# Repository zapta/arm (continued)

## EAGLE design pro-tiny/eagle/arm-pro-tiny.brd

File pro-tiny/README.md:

ARM PRO TINY
============

### OVERVIEW

TBD.

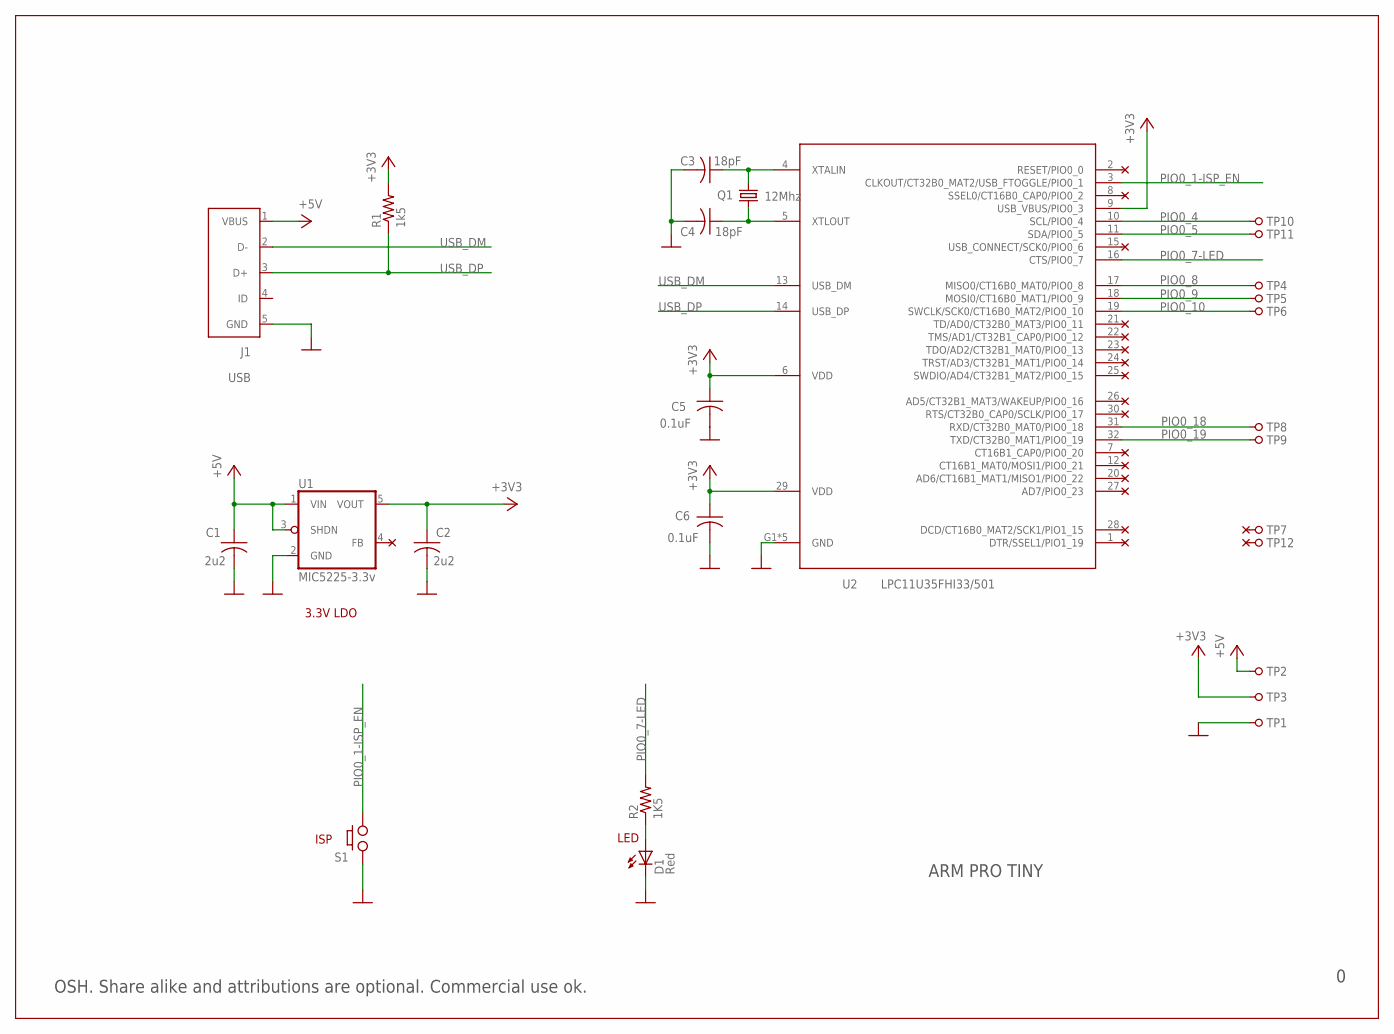
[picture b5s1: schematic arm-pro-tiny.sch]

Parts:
C1, C2: 2u2; C0402K
C3, C4: 18pF; C0402K
C5, C6: 0.1uF; C0402K
D1: Red; CHIP-LED0603
J1: USB; USB-MICRO-ZX62RD-AB-5P8
Q1: 12Mhz; CRYSTAL
R1: 1k5; R0402
R2: 1K5; R0402
S1: PUSH_BUTTON
TP1, TP2, TP3, TP4, TP5, TP6, TP7, TP8, TP9, TP10, TP11, TP12: HDR1; 1X01
U1: MIC5225-3.3v; SOT25
U2: LPC11U35FHI33/501; HVQFN33-5MM

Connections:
+3V3: C2.1, C5.1, C6.1, R1.2, TP3.1, U1.5 (VOUT), U2.6 (VDD), U2.9 (USB_VBUS/PIO0_3), U2.29 (VDD)
+5V: C1.1, J1.1 (VBUS), TP2.1, U1.1 (VIN), U1.3 (SHDN)
GND: C1.2, C2.2, C3.2, C4.2, C5.2, C6.2, D1.C, J1.5 (GND), S1.A1 (1), TP1.1, U1.2 (GND), U2.G1 (GND), U2.G2 (GND), U2.G3 (GND), U2.G4 (GND), U2.TAB (GND)
unnamed: C3.1, Q1.3 (2), U2.4 (XTALIN)
unnamed: C4.1, Q1.1, U2.5 (XTLOUT)
unnamed: D1.A, R2.1
PIO0_1-ISP_EN: S1.B2 (2), U2.3 (CLKOUT/CT32B0_MAT2/USB_FTOGGLE/PIO0_1)
PIO0_4: TP10.1, U2.10 (SCL/PIO0_4)
PIO0_5: TP11.1, U2.11 (SDA/PIO0_5)
PIO0_7-LED: R2.2, U2.16 (CTS/PIO0_7)
PIO0_8: TP4.1, U2.17 (MISO0/CT16B0_MAT0/PIO0_8)
PIO0_9: TP5.1, U2.18 (MOSI0/CT16B0_MAT1/PIO0_9)
PIO0_10: TP6.1, U2.19 (SWCLK/SCK0/CT16B0_MAT2/PIO0_10)
PIO0_18: TP8.1, U2.31 (RXD/CT32B0_MAT0/PIO0_18)
PIO0_19: TP9.1, U2.32 (TXD/CT32B0_MAT1/PIO0_19)
USB_DM: J1.2 (D-), U2.13 (USB_DM)
USB_DP: J1.3 (D+), R1.1, U2.14 (USB_DP)

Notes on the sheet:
ARM PRO TINY
ISP
LED
3.3V LDO
OSH. Share alike and attributions are optional. Commercial use ok.

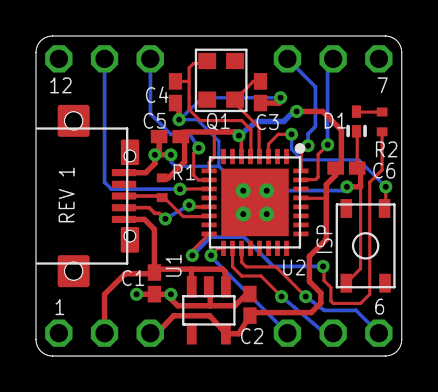
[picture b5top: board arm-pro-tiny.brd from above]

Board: 2 copper layers, 20.3 x 17.8 mm, 26 parts (0 on the bottom side), 17 nets.

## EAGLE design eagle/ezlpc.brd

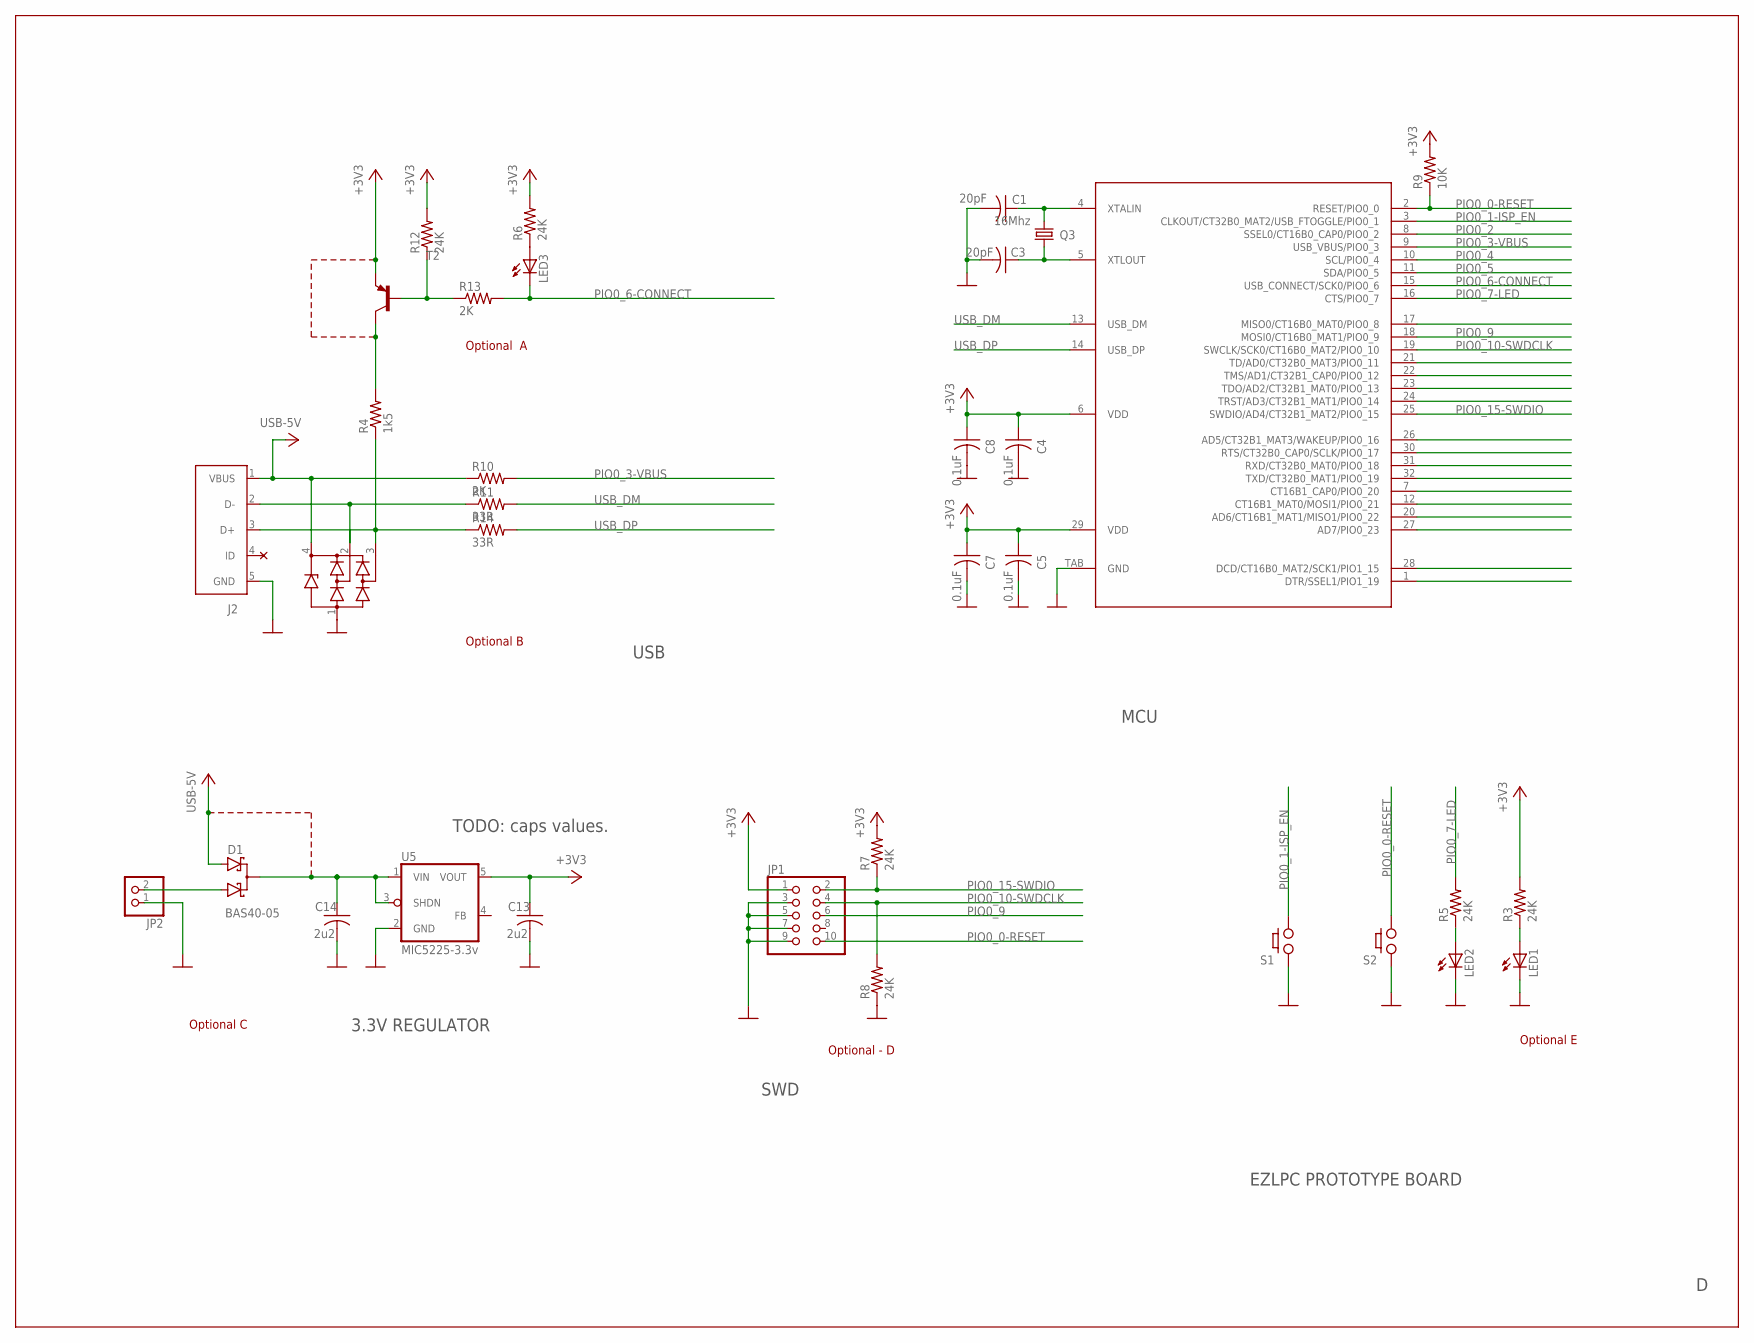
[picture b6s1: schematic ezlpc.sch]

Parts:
C1, C3: 20pF; C0603
C4, C5, C7, C8: 0.1uF; C0603
C13, C14: 2u2; C0603
D1: BAS40-05; SOT23
J2: USB; USB-MICRO-ZX62RD-AB-5P8
JP1: SWD-HEADER
JP2: PINHD-1X2; 1X02
LED1, LED2, LED3: LEDCHIP-LED0603; CHIP-LED0603
Q3: 16Mhz; CRYSTAL-CTS406
R3, R5, R6, R7, R8, R12: 24K; R0402
R4: 1k5; R0402
R9: 10K; R0402
R10, R13: 2K; R0402
R11, R14: 33R; R0402
S1, S2: PUSH_BUTTON
T2: BC857B-PNP-SOT23-BEC; SOT23-BEC
U4: LPC11U35FHN33/501; HVQFN33-5MM
U5: MIC5225-3.3v; SOT25
U$5: PRTR5VOU2X; SOT143B

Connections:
+3V3: C4.1, C5.1, C7.1, C8.1, C13.1, JP1.1, R3.2, R6.2, R7.2, R9.2, R12.2, T2.E, U4.6 (VDD), U4.29 (VDD), U5.5 (VOUT)
GND: C1.2, C3.2, C4.2, C5.2, C7.2, C8.2, C13.2, C14.2, J2.5 (GND), JP1.3, JP1.5, JP1.7, JP1.9, JP2.1, LED1.C, LED2.C, R8.1, S1.A1 (1), S2.A1 (1), U4.TAB (GND), U5.2 (GND), U$5.1 (GND)
unnamed: C1.1, Q3.1, U4.4 (XTALIN)
unnamed: LED1.A, R3.1
unnamed: C3.1, Q3.3 (2), U4.5 (XTLOUT)
unnamed: R12.1, R13.1, T2.B
unnamed: R4.2, T2.C
unnamed: LED2.A, R5.1
unnamed: LED3.A, R6.1
unnamed: J2.2 (D-), J2.3 (D+), R4.1, R11.1, R14.1, U$5.2 (IO1), U$5.3 (IO2)
unnamed: C14.1, D1.3 (C), U5.1 (VIN), U5.3 (SHDN)
unnamed: D1.1 (A1), JP2.2
PIO0_0-RESET: JP1.10, R9.1, S2.B2 (2), U4.2 (RESET/PIO0_0)
PIO0_1-ISP_EN: S1.B2 (2), U4.3 (CLKOUT/CT32B0_MAT2/USB_FTOGGLE/PIO0_1)
PIO0_2: U4.8 (SSEL0/CT16B0_CAP0/PIO0_2)
PIO0_3-VBUS: R10.2, U4.9 (USB_VBUS/PIO0_3)
PIO0_4: U4.10 (SCL/PIO0_4)
PIO0_5: U4.11 (SDA/PIO0_5)
PIO0_6-CONNECT: LED3.C, R13.2, U4.15 (USB_CONNECT/SCK0/PIO0_6)
PIO0_7-LED: R5.2, U4.16 (CTS/PIO0_7)
PIO0_9: JP1.6, U4.18 (MOSI0/CT16B0_MAT1/PIO0_9)
PIO0_10-SWDCLK: JP1.4, R8.2, U4.19 (SWCLK/SCK0/CT16B0_MAT2/PIO0_10)
PIO0_15-SWDIO: JP1.2, R7.1, U4.25 (SWDIO/AD4/CT32B1_MAT2/PIO0_15)
USB-5V: D1.2 (A2), J2.1 (VBUS), R10.1, U$5.4 (VCC)
USB_DM: R11.2, U4.13 (USB_DM)
USB_DP: R14.2, U4.14 (USB_DP)

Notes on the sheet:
TODO: caps values.
EZLPC PROTOTYPE BOARD
MCU
3.3V REGULATOR
USB
SWD
Optional B
Optional C
Optional - D
Optional E
Optional A

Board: 2 copper layers, 34 parts (0 on the bottom side), 23 nets, no tracks yet.

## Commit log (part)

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2014-10-01 First iteration of the ezlpc lib.
2014-10-01 Moved the delay function out of main.
2014-10-02 Added LPC11U3X documentation.
2014-10-06 Very early draft of the PCB.
2014-10-06 More progress with the library. Still an early draft.
2014-10-10 Initial placement.
2014-10-11 Imprived the placement. Now can auto route 100%.
2014-10-11 Extracted self library from the schema.
2014-10-12 Ready for final auto routing.
2014-10-12 More layout cleanup.
2014-10-12 Change via mask limit to 20 mils.
2014-10-12 Added layout pdf.
2014-10-14 Added BOM.
2014-10-14 Updated BOM
2014-10-14 Turned the SWD connector
2014-10-14 Tweaked the silk screen layer.
2014-10-14 Cleaned up ERC warnings.
2014-10-14 Renamed eagle files from ezlpc-proto to arm-mini-pro. Yet to do the same for the firmware.
2014-10-14 Added pdf files.
2014-10-18 Generated gerbers using Elecrow 2 layers CAM files.
2014-10-19 Added a few resources.
2014-11-07 Copied eagle files to new location (pro-mini)
2014-11-07 Updated layout pdf.
2014-11-08 Added 3D print model for a case.
2014-11-08 Added TODO file.
2014-11-08 Added lpcxpresso files.
2014-11-08 Added resource files.
2014-11-09 Assorted cleanups.
2014-11-09 Left overs from previous checkin.
2014-11-10 Fixed location of RST and ISP switches labels (were swapped in the layout). Added labels for GND, 5V and 3V3 pins. No semantic change. Made the gerber files obsolete. Will generate new ones.
2014-11-10 Minor comment change. No semantic change.
2014-12-10 Added two precompiled hello world binaries for the Getting Started procedure.
2014-12-11 Hello world now use \r\n EOL terminator for dump serial port dumpers.
2014-12-17 Added first installment of the README file. Minor BOM update.
2014-12-17 Another table experiment.
2014-12-17 Udpated quick start 1.
2014-12-17 Added link
2014-12-17 Readme update
2014-12-17 Readme updated.
2014-12-17 Readme update.
2014-12-20 Added pinout diagram (requires verification)
2014-12-20 Pintout diagram update
2014-12-20 Pinout update
2014-12-20 Tweaked the schematic, no semantic change.
2014-12-20 Updated TODO file.
2014-12-20 Readme updated
2014-12-21 Reduced 0402 resistor footprints to 0.5x0.6mm pads and 0.6mm space.
2014-12-21 Moved the SWD header slightly up to increase the clearance from the buttons.
2014-12-21 Fixed false ERC error by redfining a NC input as passive.
2014-12-21 Improved the ground plan connectivity.
2014-12-21 Generated gerbers.
2014-12-21 Updated board layout image, added link for OSHpark ordering.
2014-12-21 Cropped the layout png file.
2014-12-22 Now chunking to 64 bit packets when printing a long string over USB/Serial.
2014-12-22 Added Linux serial port instructions. Updated Mac OSX instructions to use 'cat' instead of 'screen' (simpler).
2014-12-26 Initial version of digikey BOM csv.
2014-12-26 Updated references to BOM file.
2014-12-26 Minor CSV tweak, no semantic change.
2014-12-26 Change part selection to have perfect BOM match also on Mouser.
2014-12-30 Updated and renamed pinout diagram.
2015-01-07 Added board picture with header pins.
2015-01-09 Work in progress pdf dumps.
2015-01-11 Updated gerber files.
2015-01-11 Checking in the original u8g lib in a LPCXpresso project form. Not tested yet.
2015-01-14 Renamed u8g_arm to u8g_arp_pro_mini as preperation for adaptation.
2015-01-14 More progress with the u8g driver. Needs cleanup.
2015-01-14 Added u8g hello world.
2015-01-14 Renamed project hello_u8g to u8g_example
2015-01-14 Fixed broken image link.
2015-01-14 Updated the getting started zip archive. Should include now the usb printf chunking fix.
2015-01-16 Renamed nada to tiny. Minor cleanup. Still needs work.
2015-01-17 Layout completed.
2015-01-17 Updatd license note.
2015-01-17 Updated u8g SPI pin to be compatible also with ARM PRO TINY.
2015-01-19 Added a skeleton of README
2015-01-19 Fixed file name.
2015-01-20 Made the ISP copying script parametric. Now supports any project and configuration.
2015-01-20 Added instructions for setting the external tool.
2015-01-20 Readme tweaks.
2015-01-20 Fixed a typo in the BOM.
2015-01-20 Added a where to get one? section to the readme.
2015-01-20 README tweak
2015-01-21 Simplified the u8g example
2015-01-21 Fixed a typo in the u8glib, added a link to the reference manual.
2015-01-21 Updated the TODO list file.
2015-01-21 Cleaned up the u8g example.
2015-01-24 Added comments in the isp copy script.
2015-01-24 Fixed u8glib compilation warnings. No semantic change.
2015-01-28 Tweaked youtube link
2015-01-28 Tweaked video text.
2015-01-29 Added to u8g_example a jump to ISP mode when ISP button is pressed.
2015-01-31 USB connector opening now goes all the way down to the top of the base to allow prying the board out.
2015-02-01 Added ARP PRO TINY pictures and pinout diagram.
2015-02-01 Added oled pinout for ARM PRO TINY, removed unused method.
2015-02-02 Added board self test.
2015-02-02 Fixed io pins lib, now setting pin multiplexing.
2015-02-03 Updated TODO.
2015-02-03 Branched the arm pro mini eagle files for temp work.
2015-02-06 Regenerated the library from the schema.
2015-02-06 Tweaked the layout. Ready for final auto routing.
2015-02-06 Generated gerber files.
2015-02-06 Updated bom.
2015-02-12 Added esd protection
2015-02-18 Removed the arm-tiny branch. Focusing on the full pinout pro-mini.
2015-02-18 Removed picture with 3D case.
2015-02-18 Minor BOM description tweak. No semantic change.
2015-02-24 Changed hello world to blink also the new LED.
2015-02-24 Skeleton of ESP8266 program. Based on mbed.
2015-02-24 Removed .hg directory.
2015-02-25 Now ignoring also _gitignore*
2015-02-25 Added wifi command sequencer.
2015-02-27 Wifi sequence now supports eps8266 hardware reset.
2015-02-27 Flushing latest changes.
2015-03-10 Updated green led part number. This one is brighter.
2015-03-10 Increased pogo pin holes, added RST and ISP buttons.
2015-03-24 Added diodes/cap circuit for a single button ISP. Grounded two extra pins of the crystal. Swapped the order and increase the spacing between the two buttons. Ready for final auto routing.
2015-03-24 Deprecated old gerber
2015-03-25 Tweaked the binary copying file.
2015-03-25 Bumped version number to 3. Tweaked labels.
2015-03-25 Tweaked a few traces.
2015-03-31 Very rough version. Login fails.
2015-04-01 Code cleanup
2015-04-02 Headed upstream heartbeat.
2015-04-03 Now parsing stanza message.
2015-04-03 Minor tweak of the icsp copy tool.
2015-04-03 Rename self test binary file.
2015-04-03 Checking in the lua stuff.
2015-04-03 Added a precompied usb_serial.
2015-04-03 Renamed project, mbed_wifi -> cloud_node
2015-04-04 Now parsing the key/value in the incoming messages.
2015-04-04 Added u8g library. Yet to make it to work with mbed.
2015-04-04 Renamed setup and loop to initialize and polling respectivly.
2015-04-04 Minor tweaks. Yet to add interrupt driven rx.
2015-04-05 Added TODO list.
2015-04-05 Updated TODO
2015-04-07 Improved timing. This is a stable version. Code needs cleanup.
2015-04-08 Removed obsolete files.
2015-04-11 Fixed the tester board. Updated self test for a slow LED scanning.
2015-04-11 Generated gerbers
2015-04-22 Updated documentation.
2015-04-22 Updated documentation
2015-05-14 Updated readme.
2015-05-25 Added note regarding NXP LPC11U35 reference board.
2015-06-18 Updated self test binary.
2015-06-20 Retarget _write
    Retarget the _write function to USB/Serial. To use stdio printf
    function.
2015-06-20 Moved the link2 debugger 3d files.
2015-07-04 Added vias to switch pads for added mechanicam support. Removed the solder stop of the 4 vias under the MCU. No electrical or stencil change.
2015-07-11 Deleted an obsolete file.
2015-08-07 Retarget the _read function
    Retarget the _read function to USB/Serial for stdio scanf.
2015-09-04 Windows Batch file
    Windows Batch file to copy the generated binary image of the current
    project to the ISP virtual USB disk.
2015-09-04 Quick fix for disconnection from Linux terminal
2015-09-22 Updated comments for using "scanf()"
2015-11-15 Minor tweaks, extended pads of the crystial, transistor and USB connector for easier hand soldering. Fixed 'ARM MINI PRO' label to 'ARM PRO MINI'. Most Had to move the crystal a little bit so existin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
2015-11-30 Updated links
2015-12-11 ADC simplified
    ADC header file to simplify using the Analog to Digital Converter
2015-12-24 Added 3D model for board carrier.
2015-12-27 Added PWM outputs to the pinout diagram
2015-12-27 Removed extra white space at the bottom of the pinout diagram.
2015-12-27 Added to the pinout diagram and and indication of the open drain only pins.
2015-12-27 Updated the pinout diagram, indicating that CT32B1 timer is used for system time.
2015-12-27 Removed a leftover field text in the pinout diagram.
2015-12-28 Added a mbed gcc hello world project.
2015-12-31 EEPROM Driver
    Added eeprom.h to LPCXpresso liberary. This driver is based on a similar
    driver for mbed provided by Zapta.
2016-01-19 Exact copy of a project from mbed. Yet to be cleaned up.
2016-01-20 Deleted junk files, fixed .ld file ('nano'), enabled checksum and optimizations. Project now builds.
2016-01-20 Deleted mbed_src. mbed SDK source is under the mbed_sdk project.
2016-07-22 Reformatted
2016-07-22 Copied mbed_hello_world to a new mbed_dtmf project.
2016-07-30 Working DTMF tone generator. Needs cleanup.
2016-07-30 Fix frequency typo. Minor cleanup.
2016-07-30 Tweaked the tone generator to have a predictable outout level when idling.
2016-08-05 Minor tweaks
2016-08-05 Cleaned up library component names
2016-08-05 Associated schematic parts with library parts.
2016-08-06 Removed the mounting holes. Stable placement.
2016-08-06 3D design in progress.
2016-08-07 Added mounting holes.
2016-08-07 Added holes for the two connectors. Dimensions are tentative.
2016-08-07 Fixed connector hole offset miscalculation.
2016-08-08 Added snap-fit slots on the other two sides of the base, for symetry.
2016-08-09 Added 3D model for LED standoff.
2016-08-09 Updated BOM (still needs Mouser part numbers and part references).
2016-08-09 Added row/col generation.
2016-08-09 Tweaked 3d model dimensions.
2016-08-09 Renamed scad file.
2016-08-09 Added LED hole.
2016-08-12 Critical net routing done.
2016-08-12 Added TODO
2016-08-12 Cleaned up component references.
2016-08-12 Added board label.
2016-08-13 Filled in the BOM spreadsheet.
2016-08-13 Tweaked the BOM and TODO list.
2016-08-13 Fixed phone jack footprint.
2016-08-13 Moved the USB connector 1mm away from the board edge.
2016-08-13 Tweaked LED tPlace marking.
2016-08-14 Added two cover release notches.
2016-08-14 Tweaked the LED hole size.
2016-08-15 Minor tweaks. No semantic change.
2016-08-24 Minor tweak
2016-08-24 auto .project change
2016-08-26 Skeleton R script
2016-08-26 Calibrated the time units
2016-08-27 Added FFT computation.
2016-08-27 Added wave functions.
2016-08-27 Coppied phone finder project to its actual directory.
2016-08-27 More progress with the integration. Wifi AP is now live.
2016-08-28 A few pending changes.
2016-08-28 Fine tuned the connector holes. Increased transformer clearance.
2016-08-29 Cleaned up led control. Added periodic beeps.
2016-08-29 Added documentation
2016-09-14 Updated .propject auto changes.
2016-09-15 Created ir-control project.
2016-09-18 Basic IR packets transmission works.
2016-09-24 Added eagle files. Incomplete.
2016-09-24 Generated ir-control library.
2016-09-27 More progress with the layout.
2016-09-27 Basic version with actual ir code sending.
2016-09-28 Added ir jack.
2016-09-29 Added opto couplers.
2016-09-29 Minor tweaks.
2016-09-30 Removed the shield connection of the sense connectors.
2016-09-30 Tweaks libraries (no semantic changes) and generated gerbers with sparkfun cams.
2016-10-01 Added a control state machine. Not tested yet.
2016-10-02 Added BOM file. Incomplete.
2016-10-02 Removed old gerber file.
2016-10-06 Tweaked the LED blinking logic.
2016-10-09 ir_control case, work in progress.
